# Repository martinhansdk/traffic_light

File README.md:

Toy traffic light
=================

Firmware for a toy traffic light with intrafred communication between the units.

Features
--------

* The master light sends the timing to the slaves so independent lights remain
  in sync
* Automatic mode follows a preprogrammed timing
* Manual mode allows controlling the light through a button press on the master

Electronics
-----------

  * [schematic](pcb/MCU%20board_in_foot_v2.pdf)
  * [BOM](pcb/MCU%20board_in_foot_BOM_v2.html)
  * [EAGLE schematic](pcb/MCU%20board_in_foot_v2.sch)
  * [EAGLE layout](pcb/MCU%20board_in_foot_v2.brd)

The MCU board in the foot of the traffic light contains 

  * a 3V CR2032 battery 
  * an on/off button
  * a boost converter circuit that brings the voltage up to 3.3V
  * an ATTINY84 MCU running at 4 MHz
  * a push button (master only)
  * an IR LED (master only)
  * an IR receive module (slave only)
  * a connector for connecting to the LED board
  * a few test points
  * pads for accessing the ISP port of the MCU using pogo pins

Errata for this version of the board:

  * IRSEND on wrong gpio pin, should be on PB2
  * The IR receiver module has the wrong footprint - it should be the version that looks up
  * The boost converter does not start from CR2032, but works from alkaline
  * Some silk screen is too small
  * Difficult to remove battery from battery holder
  * ISP pins are hard to use. An edge connector would be better.

  * [schematic](pcb/LEDs_in_top.pdf)
  * [BOM](pcb/LEDs_in_top_BOM.html)
  * [EAGLE schematic](pcb/LEDs_in_top.sch)
  * [EAGLE layout](pcb/LEDs_in_top.brd)

The LED board of the traffic light contains

  * red, yellow and green LEDs with resistors
  * a connector for connecting to the MCU board
  * edge connector for adding another board with pedestrian lights or similar

  * [schematic](pcb/pogo_pin_programmer_adapter.pdf)
  * [EAGLE schematic](pcb/pogo_pin_programmer_adapter.sch)
  * [EAGLE layout](pcb/pogo_pin_programmer_adapter.brd)

A special purpose pogo pin adapter board brings the footprint of the
ISP header down to a size that is small enough to fit the MCU
board. It also provides access to some debug pins.

This version does not work that well, so I'll probably find a better
solution for the next revision.

Firmware
========

The firmware is written in C.

 * Timer 0 triggers once every 1 ms and drives the light schedule
 * Timer 1 triggers once every 50us and is used by the IR receive code
 * hal/pins.h contains the macros for controlling the GPIO pins in an efficient yet readable manner

For IR communication it uses a library based on
https://github.com/shirriff/Arduino-IRremote. The source of the ATTINY C port
seems to have disappeared from the Internet, so I can't link to it.

The firmware is not feature complete yet. To do:

 * get the IR receive code working
 * implement manual mode
 * use button to select between different programs
 * autodetect master or slave mode
 * use sleep modes

Communication protocol
======================

The communication protocol is RC5 on a 36 kHz carrier frequency. An 18 bit word is sent every time:

 * `data[17]    =    1` : start bit
 * `data[16:10] = 0x5a` : command/address
 * `data[9]     = mode` : 1=manual mode, 0=automatic mode
 * `data[8:0]   = time` : unit is 0.5s

Firmware build instructions
===========================

To build the firmware on Ubuntu or Debian do the following:

    sudo apt-get install gcc-avr binutils-avr avr-libc avrdude
    git clone https://github.com/martinhansdk/traffic_light.git
    
Connect an AVR programmer such as an usbasp to the board. The
programmer has to be set to slow mode and 3.3V operation. Edit the
Makefile to change the programmer type if needed and run
    
    make clean
    make MASTER=1
    make fuse
    make flash
    
To program a slave run the above with `MASTER=0`.

To run the unittests

    make test
    
The unittests execute on the host machine.

Mechanics
=========

The mechanics have not been designed yet, but the traffic light will
be around 10 cm high. The following sketches are from the initial
brainstorming of the concept:

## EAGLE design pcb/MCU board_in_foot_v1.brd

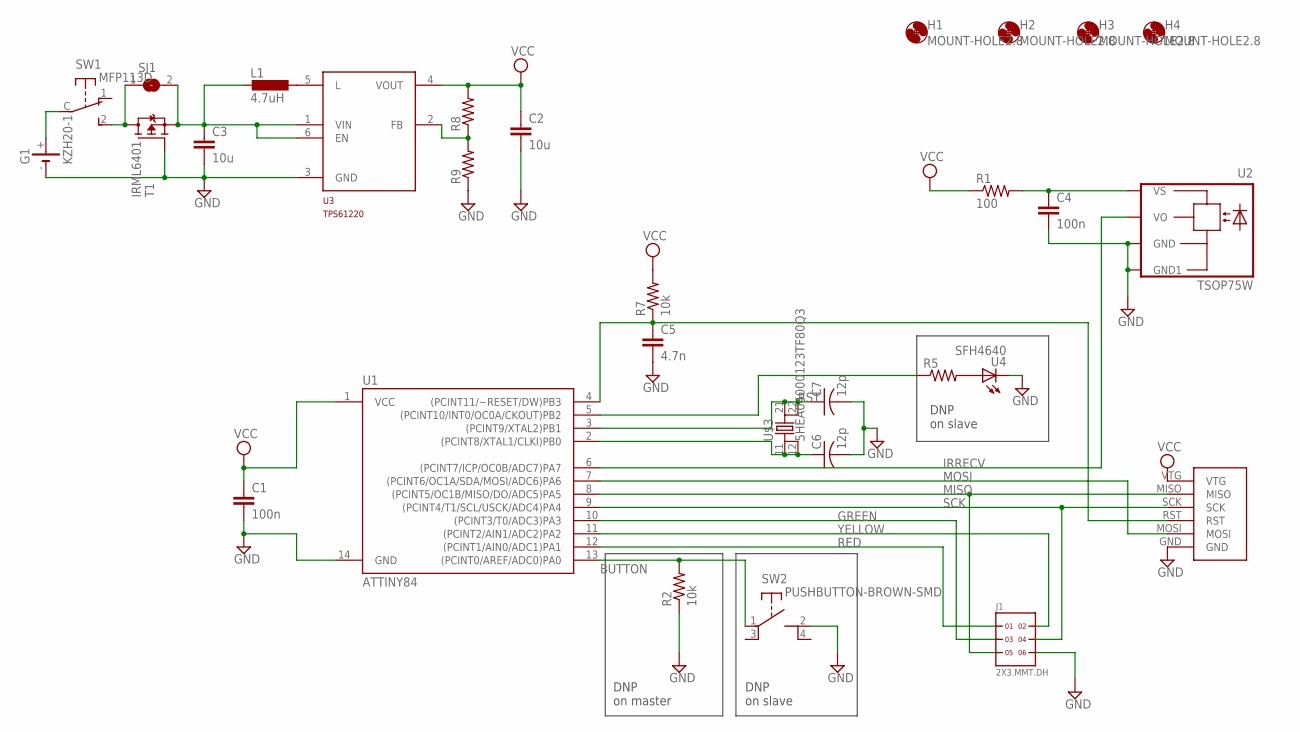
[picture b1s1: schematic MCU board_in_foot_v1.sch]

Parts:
C1, C4: 100n; 0603-CAP
C2, C3: 10u; 0603-CAP
C5: 4.7n; 0603-CAP
C6, C7: 12p; C0805
G1: KZH20-1
H1, H2, H3, H4: MOUNT-HOLE2.8; 2,8
ISP: ISP_POGOSURFACE; ISP_SURFACE
J1: 2X3.MMT.DH; 2X3_MMT.103.01.X.DH
L1: 4.7uH; EPL2010
R1: 100; R0402
R2, R7: 10k; R0402
R5: R-US_R0402; R0402
R8, R9: RESISTOR0603-RES; 0603-RES
SJ1: SJ
SW1: MFP113D; MFP-SLIDER
SW2: PUSHBUTTON-BROWN-SMD; SMD-SW
T1: IRML6401; SOT23
U1: ATTINY84; SO14
U2: TSOP75W; TSOP75W-SIDELOOK
U3: TPS61220; DCK-R_PDSO_G6
U4: SFH4640; MIDLED
U$3: 5HEA04000123TF80Q3; 10X4.5MM

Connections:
BUTTON: R2.2, SW2.1, U1.13 ((PCINT0/AREF/ADC0)PA0)
GND: C1.2, C2.2, C3.2, C4.2, C5.2, C6.2, C7.2, G1.-, ISP.GND, J1.6, R2.1, R9.1, SW2.2 (S2), T1.1 (G), U1.14 (GND), U2.1 (GND), U2.4 (GND1), U3.3 (GND), U4.K (C)
GREEN: J1.3, U1.10 ((PCINT3/T0/ADC3)PA3)
IRRECV: U1.6 ((PCINT7/ICP/OC0B/ADC7)PA7), U2.3 (VO)
IRSEND: R5.1, U1.5 ((PCINT10/INT0/OC0A/CKOUT)PB2)
MISO: ISP.MISO, J1.5, U1.8 ((PCINT5/OC1B/MISO/DO/ADC5)PA5)
MOSI: ISP.MOSI, U1.7 ((PCINT6/OC1A/SDA/MOSI/ADC6)PA6)
unnamed: L1.P$2 (2), U3.5 (L)
unnamed: SJ1.1, SW1.2 (S), T1.3 (D)
unnamed: C7.1, U1.3 ((PCINT9/XTAL2)PB1), U$3.21, U$3.22
unnamed: R8.1, R9.2, U3.2 (FB)
unnamed: C6.1, U1.2 ((PCINT8/XTAL1/CLKI)PB0), U$3.11, U$3.12
unnamed: C4.1, R1.2, U2.2 (VS)
unnamed: G1.+, SW1.C
unnamed: R5.2, U4.A
RED: J1.1, U1.12 ((PCINT1/AIN0/ADC1)PA1)
RST: C5.1, ISP.RST, R7.1, U1.4 ((PCINT11/~RESET/DW)PB3)
SCK: ISP.SCK, J1.4, U1.9 ((PCINT4/T1/SCL/USCK/ADC4)PA4)
VBAT: C3.1, L1.P$1 (1), SJ1.2, T1.2 (S), U3.1 (VIN), U3.6 (EN)
VCC: C1.1, C2.1, ISP.VTG, R1.1, R7.2, R8.2, U1.1 (VCC), U3.4 (VOUT)
YELLOW: J1.2, U1.11 ((PCINT2/AIN1/ADC2)PA2)

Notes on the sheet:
DNP on master
DNP on slave

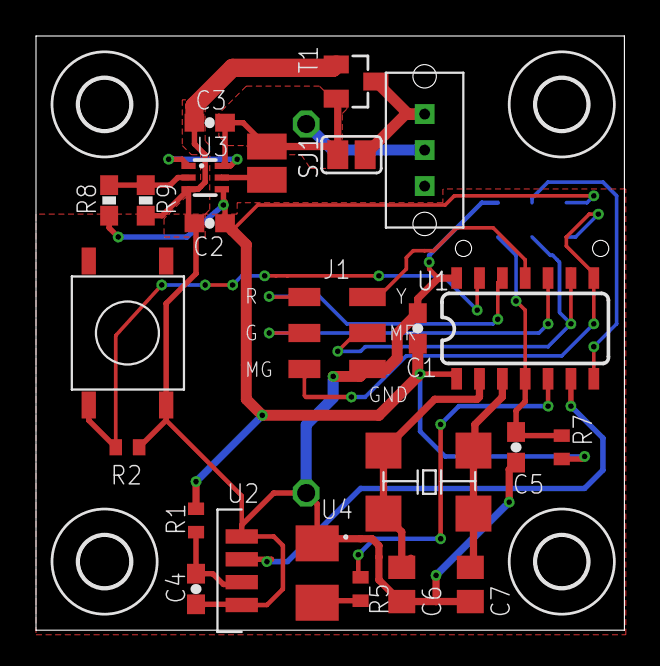
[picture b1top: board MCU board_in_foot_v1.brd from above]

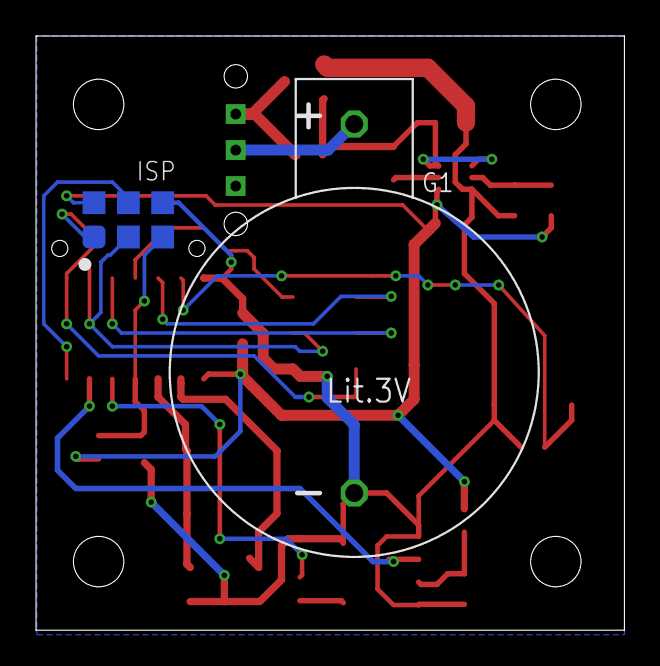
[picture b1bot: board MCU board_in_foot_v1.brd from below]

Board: 2 copper layers, 32.7 x 33.0 mm, 30 parts (2 on the bottom side), 21 nets.

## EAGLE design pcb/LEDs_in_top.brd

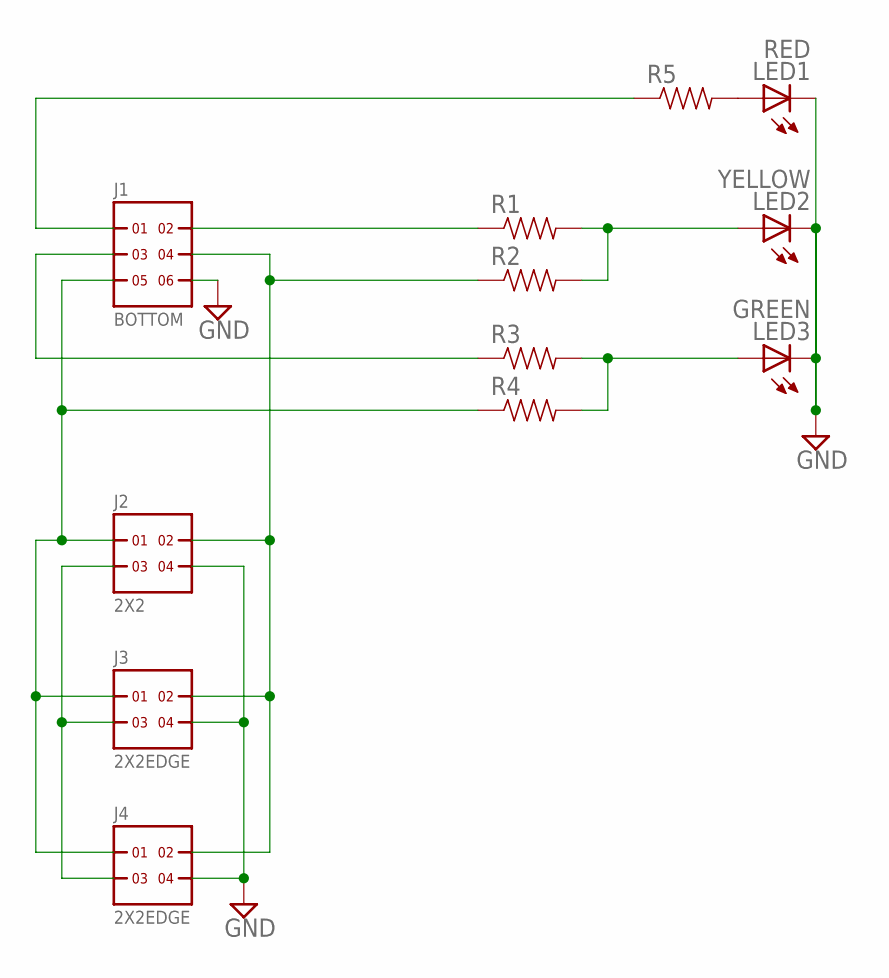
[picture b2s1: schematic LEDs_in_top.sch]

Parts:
J1: BOTTOM; 2X3-2MM-EDGE
J2: 2X2; 2X2_MMT.103.01.X.DH
J3, J4: 2X2EDGE; 2X2-2MM-EDGE
LED1: RED; CHIP-LED0805
LED2: YELLOW; CHIP-LED0805
LED3: GREEN; CHIP-LED0805
R1, R2, R3, R4, R5: RESISTOR0805-RES; 0805

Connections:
GND: J1.6, J2.4, J3.4, J4.4, LED1.C, LED2.C, LED3.C
GREEN: J1.3, R3.1
MG: J1.5, J2.1, J3.1, J4.1, R4.1
MR: J1.4, J2.2, J3.2, J4.2, R2.1
unnamed: LED3.A, R3.2, R4.2
unnamed: J2.3, J3.3, J4.3
unnamed: LED2.A, R1.2, R2.2
unnamed: LED1.A, R5.2
RED: J1.1, R5.1
YELLOW: J1.2, R1.1

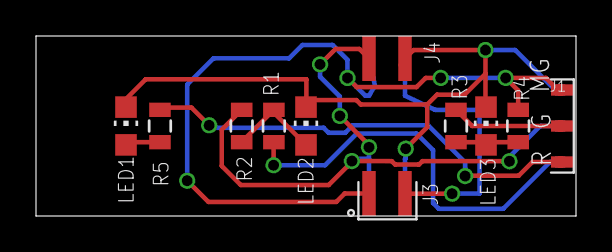
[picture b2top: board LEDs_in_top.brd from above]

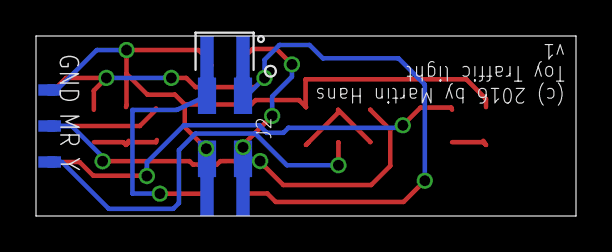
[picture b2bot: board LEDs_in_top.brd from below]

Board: 2 copper layers, 30.0 x 10.0 mm, 12 parts (2 on the bottom side), 10 nets.

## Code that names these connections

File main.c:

/******
 Implementation of a toy traffic light.

 timer 0: light scheduling and button debouncing
 timer 1: IR receive and transmit


 Pin assignments:

 PA0: IR activity indicator LED (debug)
 PA1: red LED
 PA2: yellow LED
 PA3: green LED
 PA4: ISP USCK
 PA5: ISP MISO
 PA6: ISP MOSI, IR TX
 PA7: IR RX

 PB0: XTAL1
 PB1: XTAL2
 PB2: NC
 PB3: ISP NRESET
*******/


#ifndef F_CPU
#error F_CPU not defined
#else

#if F_CPU == 4000000
#else
#error F_CPU must be 4000000
#endif

#endif

#ifndef F_OSC
#error F_OSC not defined
#endif


#include <stdbool.h>
#include <stdint.h>
#include <avr/eeprom.h>
#include <avr/io.h>
#include <avr/interrupt.h>
#include <avr/power.h>

#include "messages.h"
#include "schedule.h"
#include "debounce.h"
#include "irrecv/irrecv.h"
#include "irsend/irsend.h"
#include "hal/pins.h"
#include "pin_assignments.h"

volatile int timer_interrupt = 0;
#if MASTER == 1
bool is_master = true;
#else
bool is_master = false;
#endif
bool manual_mode = false;

/**
  light_time contains the global time which is shared by all traffic lights
  The correct state of the lights is computed from this.
  The unit is 1/2 seconds.
*/
#define TIME_UNIT_MS 500
uint16_t light_time = 0;
uint16_t cycle_time = 1;
Schedule schedule;

// P4NOSUBMIT
void save_debug_dword(uint32_t addr, uint32_t word) {
   if(eeprom_is_ready()) {
     eeprom_update_dword((uint32_t*)addr, word);
   }
}


void set_lights(uint16_t light_time) {
  const LightPattern* pattern = currentPattern(&schedule, light_time);

  if(pattern->red) pin_high(RED_PIN); else pin_low(RED_PIN);
  if(pattern->yellow) pin_high(YELLOW_PIN); else pin_low(YELLOW_PIN);
  if(pattern->green) pin_high(GREEN_PIN); else pin_low(GREEN_PIN);
}

void handle_ir_commands(const decode_results *irdata) {

  unsigned long value = irdata->value;
  save_debug_dword(0, value);
  save_debug_dword(4, extract_command(value));
  save_debug_dword(12, MESSAGE_WIDTH);

  pin_toggle(RED_PIN);
  switch(extract_command(value)) {
  case IR_SYNC_CMD:
    extract_sync_message(value, &manual_mode, &light_time);
    save_debug_dword(8, light_time);
    pin_toggle(YELLOW_PIN);
    break;
  default:
    break;
  }
}

bool RawKeyPressed() {
    return get_input(BUTTON_PIN);
}

// timer compare interrupt service routine, called once every 1 ms
uint16_t timer_int_count = 0;

ISR(TIM0_COMPA_vect)
{
  bool button_changed, button_pressed;

  timer_int_count++;
  if(timer_int_count >= TIME_UNIT_MS) {
      timer_interrupt = 1;
      timer_int_count = 0;
  }

  DebounceSwitch(&button_changed, &button_pressed);
}

decode_results irdata = {
    .value = 0
};

int main() {
#if F_OSC == 4000000
  // system clock = oscillator/1 = 4 MHz
  clock_prescale_set(clock_div_1);
#elif F_OSC == 8000000
  // system clock = oscillator/2 = 4 MHz
  clock_prescale_set(clock_div_2);
#elif F_OSC == 16000000
  // system clock = oscillator/4 = 4 MHz
  clock_prescale_set(clock_div_4);
#else
#error Unsupported F_OSC
#endif

  // define schedule
  int i = 0;

  setPattern(&schedule, i++, 2*2, true, true, false); // yellow/red
  setPattern(&schedule, i++, 18*2, false, false, true); // green
  setPattern(&schedule, i++, 4*2, false, true, false); // yellow
  // the duration of the red signal must be just so long that the light pointing
  // in the other direction can cycle through yellow-green-yellow plus a
  // little margin where both are red
  setPattern(&schedule, i, 0, false, false, false); // temporary end marker, remove this when beginning to make intersections
  uint16_t red_duration = cycleTime(&schedule) + 1*2;
  setPattern(&schedule, i++, red_duration, true, false, false); // red
  setPattern(&schedule, i, 0, false, false, false); // end marker

/*
  setPattern(&schedule, i++, 1*2, false, true, false); // yellow
  setPattern(&schedule, i++, 1*2, false, false, false); // off
  setPattern(&schedule, i, 0, false, false, false); // end marker
*/

  cycle_time = cycleTime(&schedule);


  // Set LED ports to output
  set_dir_out(RED_PIN);
  set_dir_out(YELLOW_PIN);
  set_dir_out(GREEN_PIN);

  pin_high(RED_PIN);
  pin_high(GREEN_PIN);
  
  // initialize timer0, trigger compare interrupt once every 1 ms
  TCCR0A = 0x02;      // Clear Timer on Compare Match (CTC) mode
  TIFR0 |= 0x01;      // clear interrupt flag
  TIMSK0 = 0x02;      // TC0 compare match A interrupt enable
  TCCR0B = 0x03;      // clock source CLK/64, start timer

#if F_CPU == 4000000
  OCR0A  = 62;        // number to count up to
#else
#error Unsupported F_CPU
#endif

  setup_irrecv();

  sei();             // enable all interrupts

  while(1) {
      // wait until timer isr was run
      while(true) {
        if (irrecv_decode(&irdata)) {
          handle_ir_commands(&irdata);
          irrecv_resume();
        }
        if(timer_interrupt) break;
      }
      timer_interrupt = 0;

      light_time++;

      if(light_time >= cycle_time) {
        light_time %= cycle_time;
      }

      if(is_master) {
        //irsend_sendRC5( make_sync_message(manual_mode, light_time), MESSAGE_WIDTH); P4NOSUBMIT
        irsend_sendRC5( make_sync_message(manual_mode, 0x155), MESSAGE_WIDTH);
        save_debug_dword(0, make_sync_message(manual_mode, 0x155));
        save_debug_dword(4, make_sync_message(manual_mode, 0x155) & 0x3ffff);
      }

      if(is_master) // P4NOSUBMIT
      set_lights(light_time);
  }
}

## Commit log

2015-01-26 Adds makefile and dummy main program
2015-01-27 simple traffic light application with no communication
2015-01-28 Define more sensible timing
2015-01-30 add an implementation of RC5 send/receive to see how much space that would take
2015-02-01 Arduino version, using timer 1.
2015-02-01 Move towards a programmable schedule.
2015-02-01 Implemented all receive IR commands, RAM only.
2015-02-06 added debouncing function
2015-02-06 port the Arduino version to bare bones C
2015-02-06 ported the sending portion of the IRRemote library
    Also, GCC will now remove unused code from the final binary, resulting in noticable space savings.
2015-02-06 add debounce logic for button - not debugged, just added to get an idea of code size
2015-02-06 adjust timer interrupt to trigger every 1 ms
2015-02-06 made avrdude work, use 8MHz internal clock for now
2015-02-06 make timer 0 interrupt work and fix LED output
2015-02-06 fix schedule time wrap around
2015-02-06 switch to 4MHz external clock
2015-02-06 adjust counter value slightly
    remove unused defines
2015-02-09 nicer way of defining pin assignments
    With these macros, it is possible to define which port and pin
    is used for a function in one place. Previously, if a function
    was moved to a pin on a different port, it was necessary to
    hunt down all the places the pin was referenced and change
    the port register. The macros take care of this now.
2015-02-09 add travis ci script
2015-02-09 better readme
2015-02-09 fix link to build status png
2015-02-27 Switch to internal RC clock (calibrated)
2015-03-01 Fix that "make clean" would delete debounce.c
    Switch to internal RC oscillator, system clock at 4 MHz.
    Master sends time and mode every 500ms.
2018-07-17 Change pin assignment to match the PCB
2018-07-25 Switch to usbasp as programmer and allow selecting master/slave from makefile.
2018-07-27 Make sure system clock is always 4 MHz
2018-07-28 WIP making recv work
2018-11-06 Properly document the current state of the project and add PCB files
2018-11-09 Fix construction of the command word.
    Some of the bit shifting math did not work because an int is 16 bits
    and some of the bit shifting math ended up shifting the data out of
    this range.
2018-11-09 Factor encoding and decoding of messages into it's own file.
2018-11-09 ISO C forbids breaced-groups within expressions
2018-11-09 Add unittest for the message encoding/decoding.
2018-11-09 Force C++11 for unittests.
2018-11-09 Fix wrong gcc command line switch
2018-11-09 Model the truncation of the IR word in the unit test.
2018-12-22 WIP debug communication

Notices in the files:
pcb/LEDs_in_top.brd:
(c) 2016 by Martin Hans
pcb/MCU board_in_foot_v1.brd:
(c)2015 Martin Hans
parts and their libraries:
SparkFun-Passives: Licensing: Creative Commons ShareAlike 4.0 International - https://creativecommons.org/licenses/by-sa/4.0
